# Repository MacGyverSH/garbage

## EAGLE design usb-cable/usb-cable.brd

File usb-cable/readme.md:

# USB Charging Cable

This is small breakout pcb for USB A connector with USB charging controller IC *TPS2514*. 

## BOM

- [TPS2514](http://www.ti.com/product/TPS2514/technicaldocuments)
- USB A connector [87520-0010BLF](https://cz.mouser.com/ProductDetail/649-87520-0010BLF)
- 2 pin connector [Phoenix Contact MSTBA2](https://cz.mouser.com/ProductDetail/Phoenix-Contact/1757242?qs=sGAEpiMZZMvlX3nhDDO4AOG7PuaOf7seqSfc9r0Vy5w%3d)
- 100nF cap (0805)
- LED (0805) + resistor (0805)

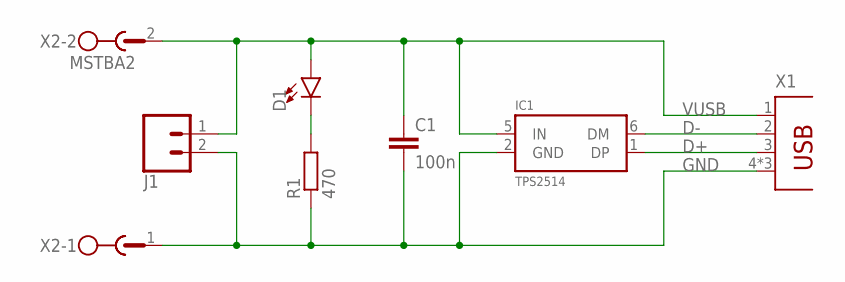
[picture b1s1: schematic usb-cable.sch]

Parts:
C1: 100n; C1206K
D1: LED0805-RESISTOR-PACKAGE; LED-0805
IC1: TPS2514; SOT23-6
J1: CONN_02; 1X02
R1: 470; R0805
X1: PN87520
X2: MSTBA2

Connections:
D+: IC1.1 (DP), X1.3
D-: IC1.6 (DM), X1.2
GND: C1.2, IC1.2 (GND), J1.2, R1.1, X1.4, X1.S1 (4), X1.S2 (4), X2.1
unnamed: D1.2 (C), R1.2
VUSB: C1.1, D1.1 (A), IC1.5 (IN), J1.1, X1.1, X2.2

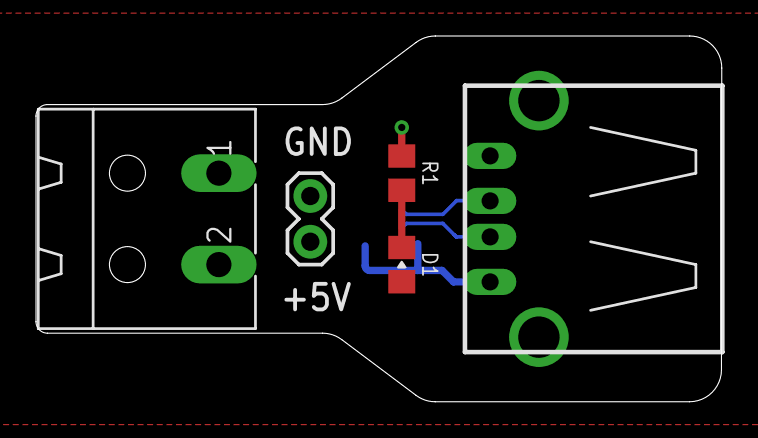
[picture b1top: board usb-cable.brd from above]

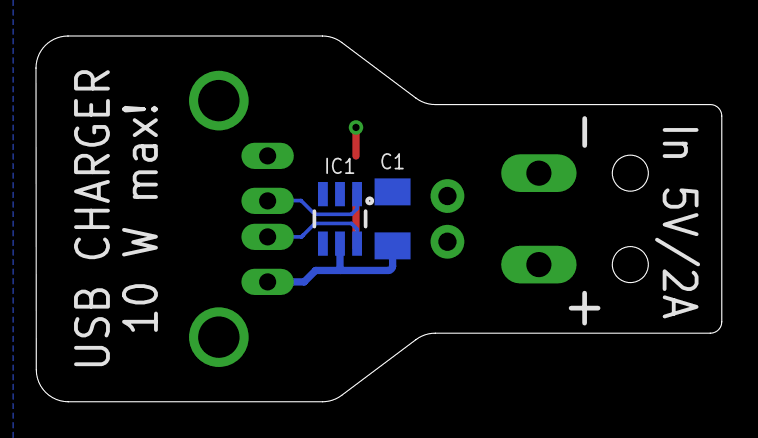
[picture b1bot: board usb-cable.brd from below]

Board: 2 copper layers, 38.1 x 20.3 mm, 7 parts (2 on the bottom side), 5 nets.

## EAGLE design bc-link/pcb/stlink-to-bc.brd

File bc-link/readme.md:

# BC-Link

*Simple adapter board between cheap Chinese ST-Link V2 clone and [**BigClown's Core Module**](https://doc.bigclown.com/core-module.html).*

## A Few Notes

- PCB is double sided but can be assembled without plated vias (friendly for homebrew PCB)
- [0.05" Connector](http://www.digikey.com/products/en?lang=en&vendor=0&WT.z_cid=ref_findchips0311_dkc_buynow&mpart=20021521-00010T1LF&cur=USD) and cable came from MS Gadgeteer
- There is one jumper for connect/disconnect Vdd

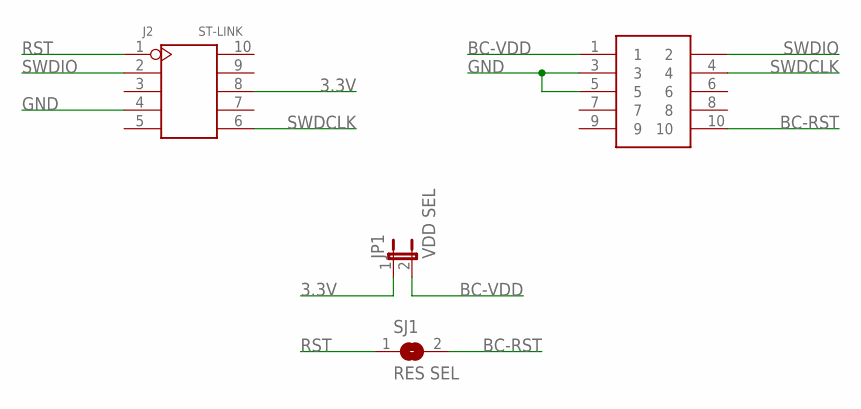
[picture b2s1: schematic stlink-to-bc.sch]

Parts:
J1: BC; SHF105DSM_1
J2: ST-LINK; V2X5-2.54
JP1: VDD SEL; JP1
SJ1: RES SEL; SJ

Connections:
3.3V: J2.8, JP1.1
BC-RST: J1.10, SJ1.2
BC-VDD: J1.1, JP1.2
GND: J1.3, J1.5, J2.4
RST: J2.1, SJ1.1
SWDCLK: J1.4, J2.6
SWDIO: J1.2, J2.2

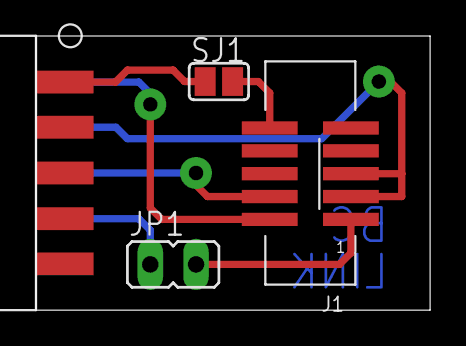
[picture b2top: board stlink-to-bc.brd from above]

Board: 2 copper layers, 21.9 x 15.2 mm, 4 parts (0 on the bottom side), 7 nets.

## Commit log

2015-01-07 gVictor
2015-01-07 WTFPL
2017-02-23 Add BC-Link
2017-02-23 Fix foto
2017-02-23 Remove big photo
2018-07-31 Add ESP display
2018-07-31 Add USB Cable PCB
2018-07-31 Update .gitignore to ignore Eagle's files

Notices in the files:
parts and their libraries:
SparkFun-Connectors: Licensing: Creative Commons ShareAlike 4.0 International - https://creativecommons.org/licenses/by-sa/4.0
